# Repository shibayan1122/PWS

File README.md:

# PWS(Personal Wireless Studio)

---
Maker Faire Tokyo 2016 <http://makezine.jp/event/mft2016/> のヤマハ(株)ブースにて展示を行った、ギター向けIoTデバイス(PWS: Personal Wireless Studio)のハードウェア開発資料・ソフトウェア一式を公開しています。  
PWS の制作方法に関しては、Fabble のプロジェクトページ <http://fabble.cc/yamahafsm/craft-iot-guitar> をご参照下さい。

## ディレクトリ
### hardware
パネル基板の設計図、部品表などを公開しています。

### software
PWS を動作させるのに必要なソフトウェア一式を公開しています。

## 著作権とライセンス
**Copyright (c) 2016 Yamaha Corporation released under the MIT license.**  
このソフトウェアは、MITライセンスのもとで公開しています。詳しくは LICENSE をご参照ください。  
(This software is released under the MIT License, see LICENSE.)

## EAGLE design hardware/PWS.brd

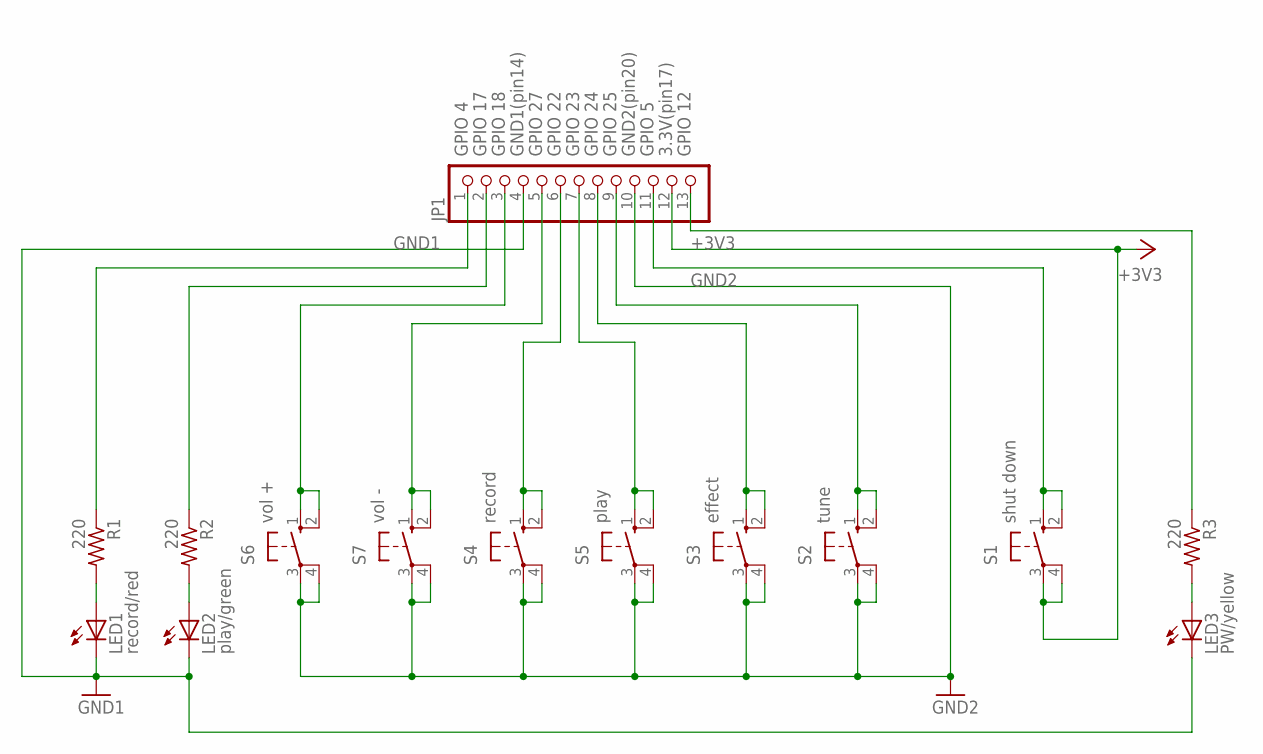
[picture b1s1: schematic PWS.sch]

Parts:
JP1: PINHD-1X13; 1X13
LED1: record/red; LED3MM
LED2: play/green; LED3MM
LED3: PW/yellow; LED3MM
R1, R2, R3: 220; 0204/5
S1: shut down; B3F-10XX
S2: tune; B3F-10XX
S3: effect; B3F-10XX
S4: record; B3F-10XX
S5: play; B3F-10XX
S6: vol +; B3F-10XX
S7: vol -; B3F-10XX

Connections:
+3V3: JP1.12, S1.3, S1.4 (P1)
GND1: JP1.4, LED1.K (C), LED2.K (C), LED3.K (C)
GND2: JP1.10, S2.3, S2.4 (P1), S3.3, S3.4 (P1), S4.3, S4.4 (P1), S5.3, S5.4 (P1), S6.3, S6.4 (P1), S7.3, S7.4 (P1)
unnamed: LED1.A, R1.2
unnamed: LED2.A, R2.2
unnamed: LED3.A, R3.2
unnamed: JP1.5, S7.1 (S), S7.2 (S1)
unnamed: JP1.3, S6.1 (S), S6.2 (S1)
unnamed: JP1.8, S3.1 (S), S3.2 (S1)
unnamed: JP1.7, S5.1 (S), S5.2 (S1)
unnamed: JP1.9, S2.1 (S), S2.2 (S1)
unnamed: JP1.11, S1.1 (S), S1.2 (S1)
unnamed: JP1.13, R3.1
unnamed: JP1.6, S4.1 (S), S4.2 (S1)
unnamed: JP1.2, R2.1
unnamed: JP1.1, R1.1

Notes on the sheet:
GPIO 4
GPIO 17
GPIO 12
GPIO 5
GPIO 25
GPIO 24
GPIO 22
GPIO 23
GPIO 18
GPIO 27
GND1(pin14)
GND2(pin20)
3.3V(pin17)

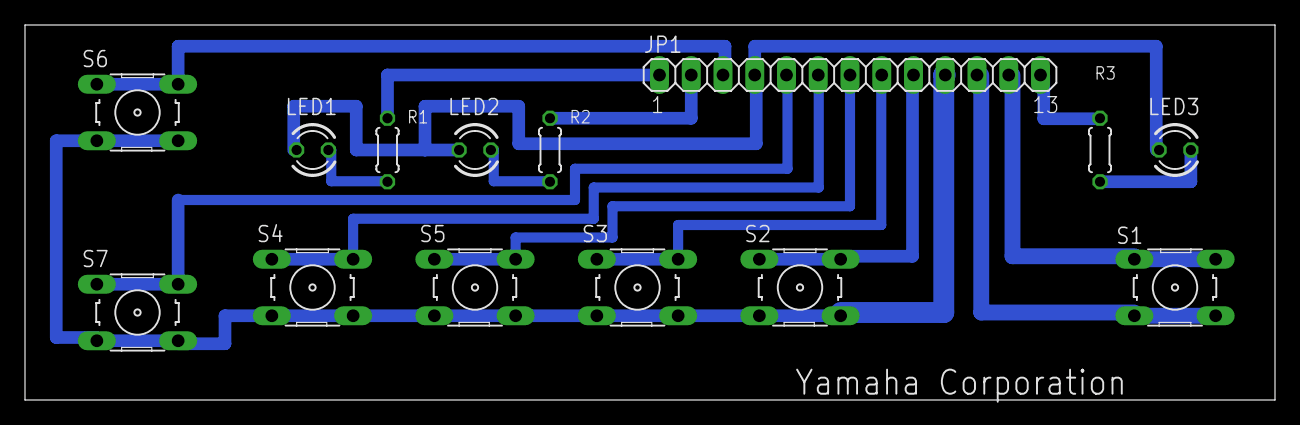
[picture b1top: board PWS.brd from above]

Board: 2 copper layers, 100.0 x 30.0 mm, 14 parts (0 on the bottom side), 16 nets.
